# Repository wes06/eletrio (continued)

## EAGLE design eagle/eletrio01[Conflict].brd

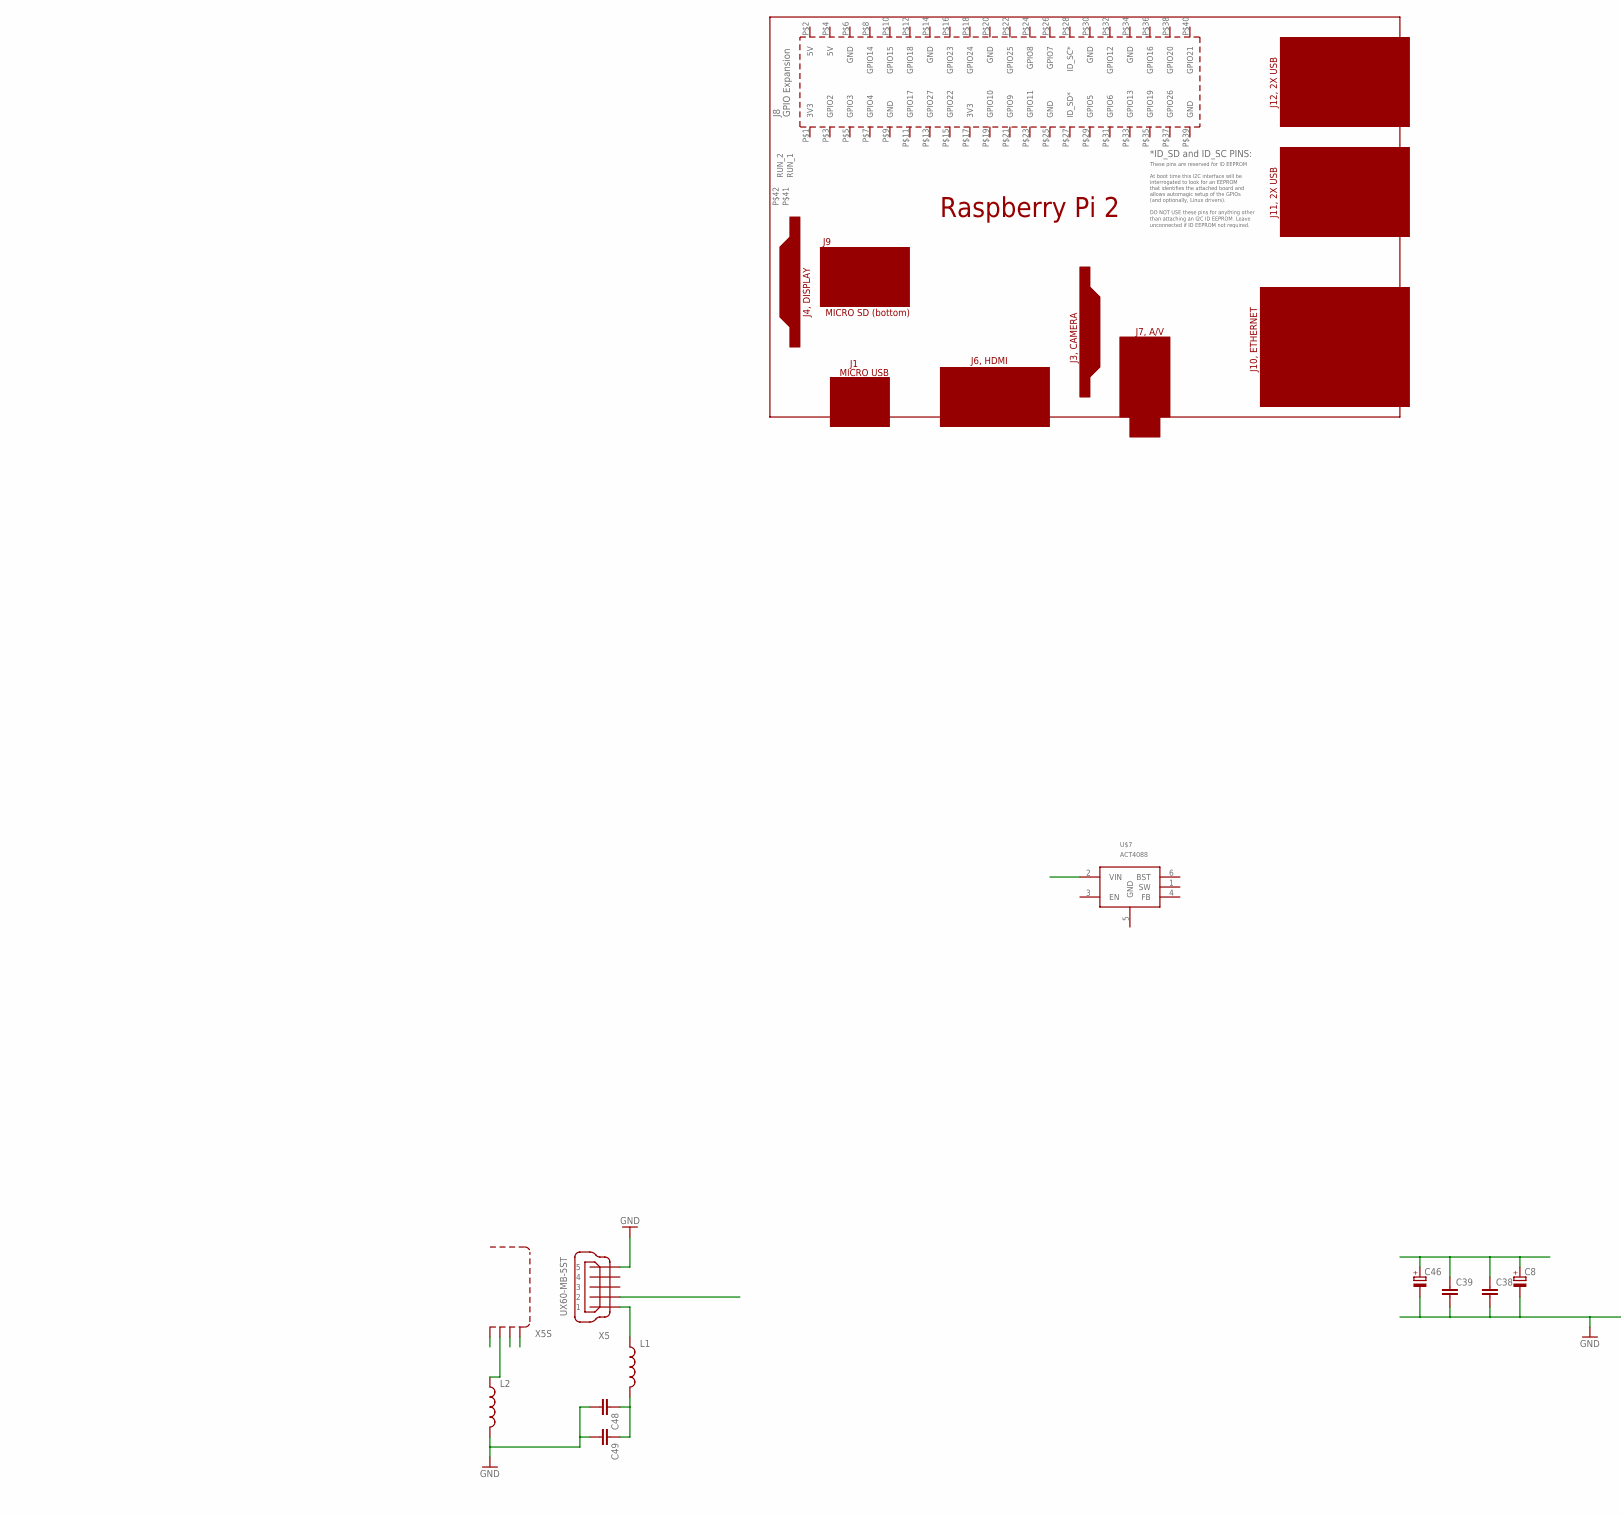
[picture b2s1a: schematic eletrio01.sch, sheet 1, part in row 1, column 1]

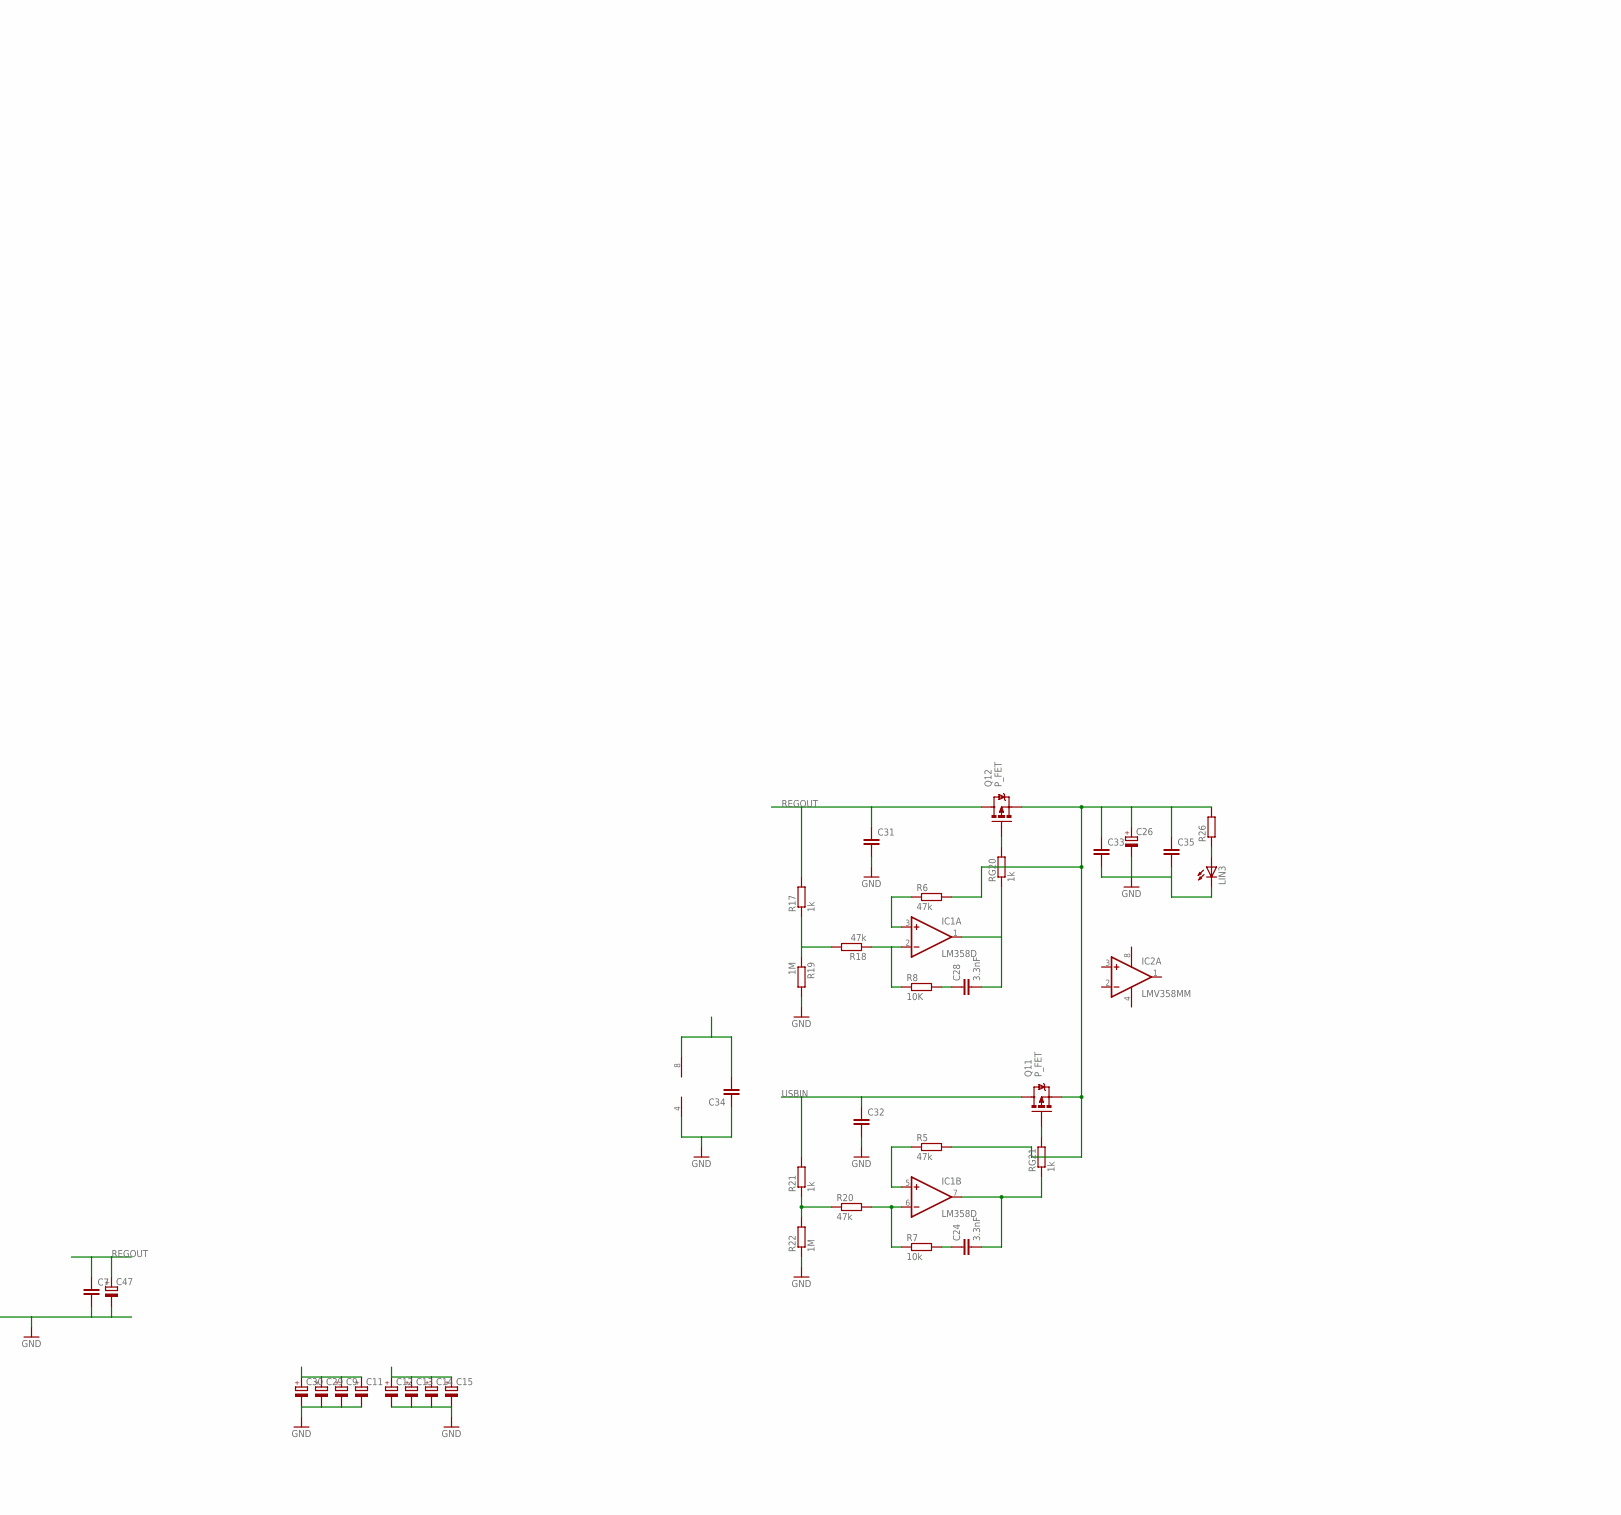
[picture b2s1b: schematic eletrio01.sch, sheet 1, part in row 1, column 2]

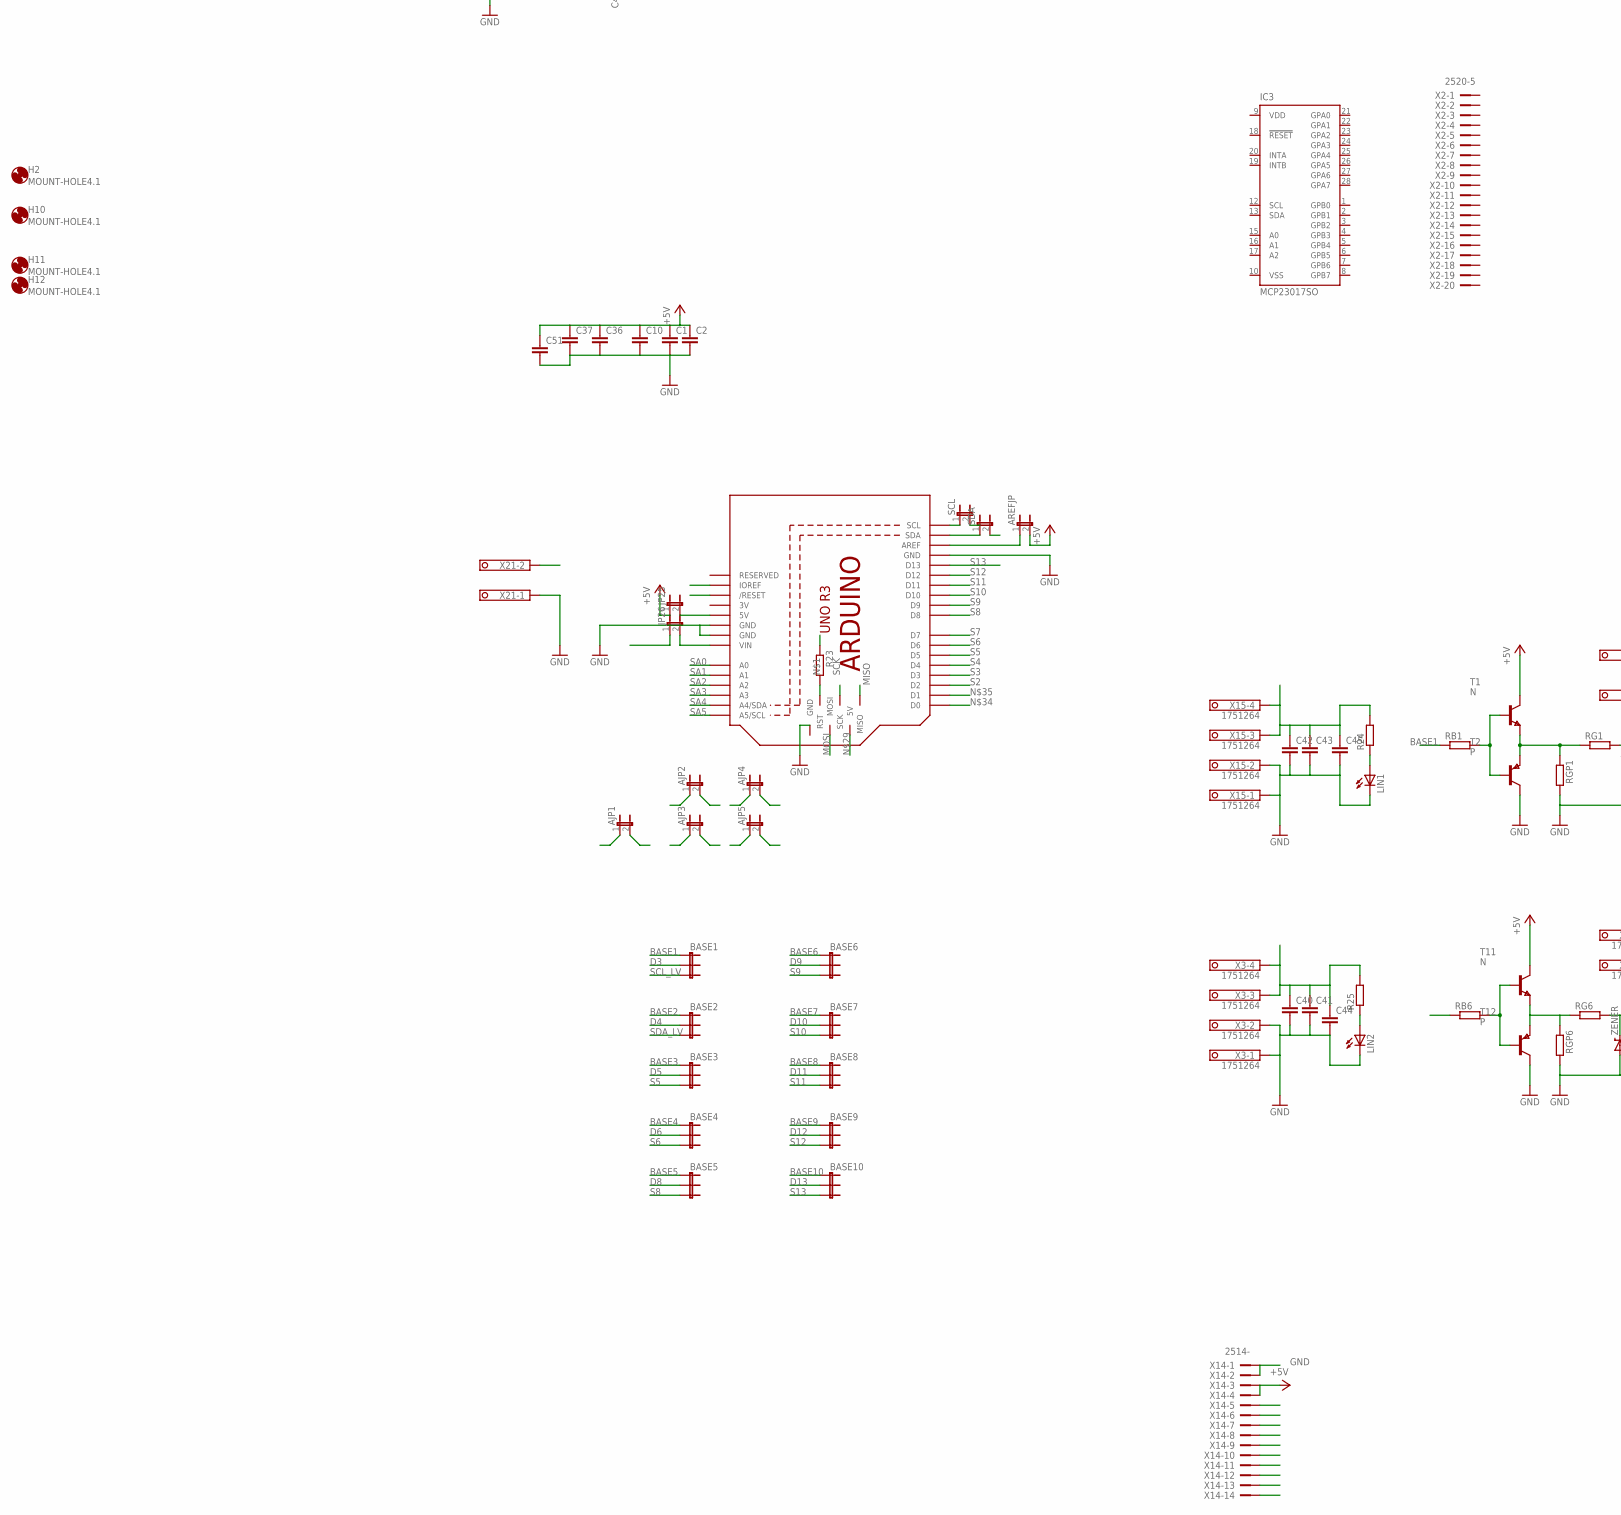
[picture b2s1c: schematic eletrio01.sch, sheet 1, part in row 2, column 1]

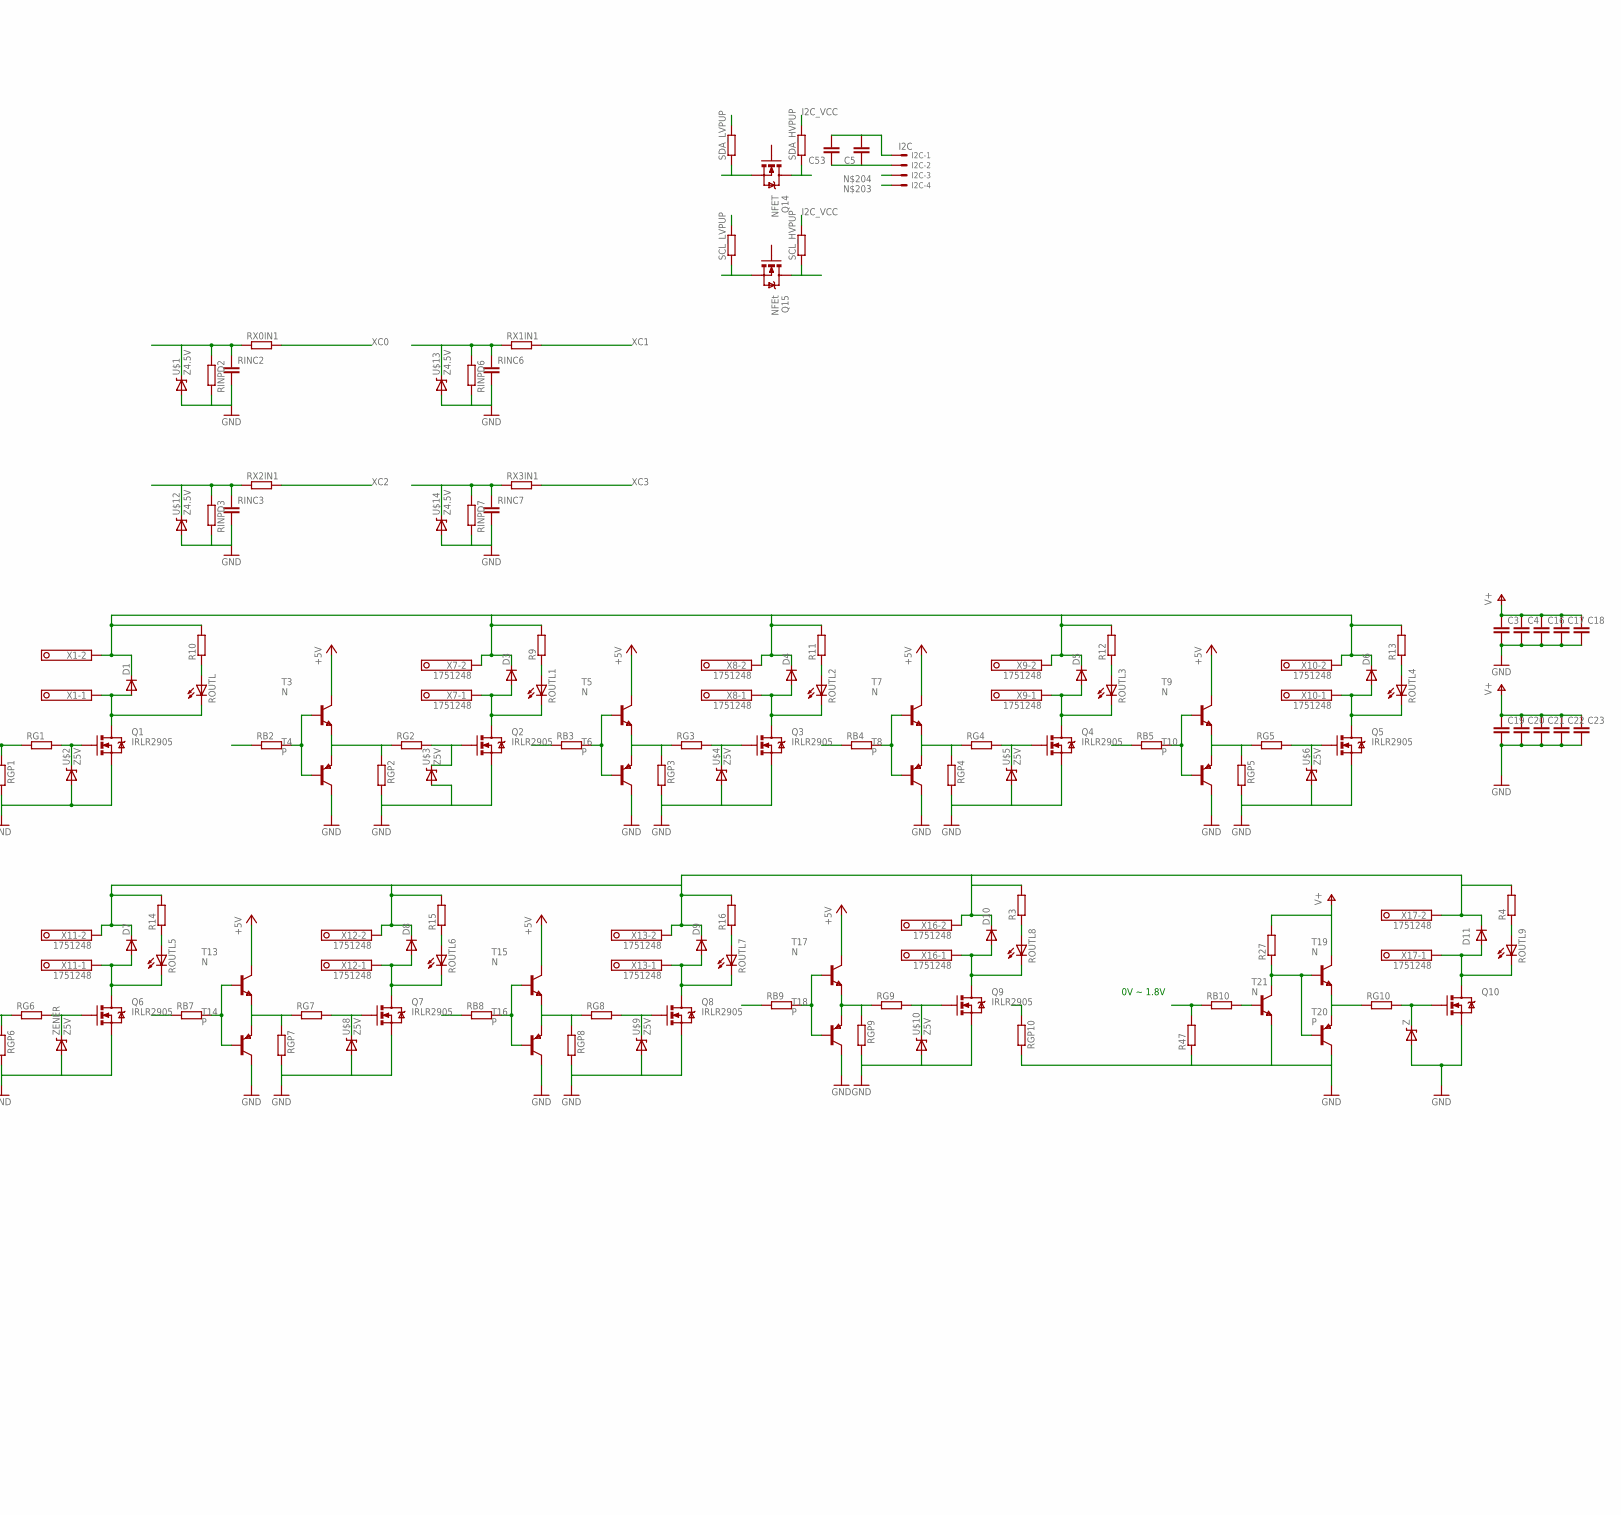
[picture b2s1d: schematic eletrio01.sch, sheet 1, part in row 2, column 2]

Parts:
AJP1, AJP2, AJP3, AJP4, AJP5: JUMPER-2SMD-NC; SJ_2S
AREFJP: JUMPER-2SMD-NC; SJ_2S
BASE1, BASE2, BASE3, BASE4, BASE5, BASE6, BASE7, BASE8, BASE9, BASE10: JUMPER-3PTH; 1X03
C1, C2, C5, C7, C10, C31, C32, C33, C34, C37, C38, C39, C40, C41, C42, C43, C48, C53: C-EUC0805; C0805
C3, C4, C16, C17, C18, C19, C20, C21, C22, C23: C-EUC0603; C0603
C8, C26, C46, C47: CPOL-EUUD-6,3X8,8; UD-6,3X5,8_NICHICON
C9, C11, C12, C13, C14, C15, C29, C30: CPOL-EUF; PANASONIC_F
C24, C28: 3.3nF; C0603
C35, C36, C49, C51: C-EUC1210; C1210
C44, C45: C-EU075-032X103; C075-032X103
D1, D3, D4, D5, D6, D7, D8, D9, D10, D11: DIODESMA-ALT; SMA-DIODE_ALT
H2, H10, H11, H12: MOUNT-HOLE4.1; 4,1
I2C: I2C; 22-23-2041
IC1: LM358D; SO08
IC2: LMV358MM; MSOP08
IC3: MCP23017SO; SO28W
JP25, JP26: JUMPER-2SMD-NC; SJ_2S
L1, L2: INDUCTOR0805; 0805
LIN1, LIN2, LIN3: LEDCHIP-LED0805; CHIP-LED0805
M1: ARDUINO_R3_ICSP; ARDUINOR3_ICSP
PCB1: RPI2
Q1, Q2, Q3, Q4, Q5, Q6, Q7, Q8, Q9: IRLR2905; DPAK
Q10: MOSFET-NCHANNELSI7820DN; POWERPAK1212-8
Q11, Q12: P_FET; SOT23-3
Q14: NFET; SOT23
Q15: NFEt; SOT23
R3, R4, R9, R10, R11, R12, R13, R14, R15, R16, R23, R24, R25, R26, R27, R47: R-EU_R0603; R0603
R5, R6, R18, R20: 47k; R0603
R7: 10k; R0603
R8: 10K; R0603
R17, R21: 1k; R0603
R19, R22: 1M; R0603
RB1, RB2, RB3, RB4, RB5, RB6, RB7, RB8, RB9, RB10: R-EU_R0603; R0603
RG1, RG2, RG3, RG4, RG5, RG6, RG7, RG8, RG9, RG10: R-EU_R0603; R0603
RG20, RG21: 1k; R0603
RGP1, RGP2, RGP3, RGP4, RGP5, RGP6, RGP7, RGP8, RGP9, RGP10: R-EU_R0603; R0603
RINC2, RINC3, RINC6, RINC7: C-EUC0805; C0805
RINPD2, RINPD3, RINPD6, RINPD7: R-EU_R0603; R0603
ROUTL, ROUTL1, ROUTL2, ROUTL3, ROUTL4, ROUTL5, ROUTL6, ROUTL7, ROUTL8, ROUTL9: LEDCHIP-LED0805; CHIP-LED0805
RX0IN1, RX1IN1, RX2IN1, RX3IN1: R-EU_R0805; R0805
SCL: JUMPER-2SMD-NC; SJ_2S
SCL_HVPUP: R-EU_R0805; R0805
SCL_LVPUP: R-EU_R0805; R0805
SDA: JUMPER-2SMD-NC; SJ_2S
SDA_HVPUP: R-EU_R0805; R0805
SDA_LVPUP: R-EU_R0805; R0805
T1, T3, T5, T7, T9, T11, T13, T15, T17, T19, T21: N; SOT323
T2, T4, T6, T8, T10, T12, T14, T16, T18, T20: P; SOT323
U$1, U$12, U$13, U$14: Z4.5V; SOD-323
U$2, U$3, U$4, U$5, U$6, U$8, U$9, U$10: Z5V; SOD-323
U$7: ACT4088; SOT23-6
X1, X7, X8, X9, X10, X11, X12, X13, X16, X17, X21: 1751248
X2: 2520-5; PAK100/2500-5-20
X3, X15: 1751264
X5: UX60-MB-5ST
X14: 2514-; PAK100/2500-14
Z: DIODE-ZENER-BZT52; SOD-323
ZENER: Z5V; SOD-323

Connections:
3V: M1.3V
+5V: AREFJP.2, C1.1, C2.1, C10.1, C26.+, C33.1, C34.2, C35.1, C36.1, C37.1, C51.1, IC1.8 (V+), JP25.1, Q11.2 (S), Q12.2 (S), R5.2, R6.2, R26.2, T1.1 (C), T3.1 (C), T5.1 (C), T7.1 (C), T9.1 (C), T11.1 (C), T13.1 (C), T15.1 (C), T17.1 (C), X14.3, X14.4
A1: AJP1.2
A2: AJP2.2
A3: AJP3.2
A4: AJP4.2, SDA.2
A5: AJP5.2, SCL.2
ARDVIN: C8.+, C38.1, C39.1, C46.+, JP26.1, X21.2
BASE1: BASE1.1, RB1.1, X14.5
BASE2: BASE2.1, RB2.1, X14.6
BASE3: BASE3.1, RB3.1, X14.7
BASE4: BASE4.1, RB4.1, X14.8
BASE5: BASE5.1, RB5.1, X14.9
BASE6: BASE6.1, RB6.1, X14.10
BASE7: BASE7.1, RB7.1, X14.11
BASE8: BASE8.1, RB8.1, X14.12
BASE9: BASE9.1, RB9.1, X14.13
BASE10: BASE10.1, RGP10.1, X14.14
D3: BASE1.2
D4: BASE2.2
D5: BASE3.2
D6: BASE4.2
D8: BASE5.2
D9: BASE6.2
D10: BASE7.2
D11: BASE8.2
D12: BASE9.2
D13: BASE10.2
GND: C3.2, C4.2, C5.2, C7.2, C8.-, C9.-, C11.-, C12.-, C13.-, C14.-, C15.-, C16.2, C17.2, C18.2, C19.2, C20.2, C21.2, C22.2, C23.2, C26.-, C29.-, C30.-, C31.2, C32.2, C33.2, C34.1, C35.2, C38.2, C39.2, C40.2, C41.2, C42.2, C43.2, C44.2, C45.2, C46.-, C47.-, C48.2, C49.2, C53.2, I2C.1, IC1.4 (V-), L2.2, LIN1.C, LIN2.C, LIN3.C, M1.GND, M1.GND@1 (GND), M1.GND@3 (GND), Q1.3 (S), Q2.3 (S), Q3.3 (S), Q4.3 (S), Q5.3 (S), Q6.3 (S), Q7.3 (S), Q8.3 (S), Q9.3 (S), Q10.S1 (S), Q10.S2 (S), Q10.S3 (S), R19.2, R22.1, R47.1, RGP1.2, RGP2.2, RGP3.2, RGP4.2, RGP5.2, RGP6.2, RGP7.2, RGP8.2, RGP9.2, RGP10.2, RINC2.2, RINC3.2, RINC6.2, RINC7.2, RINPD2.2, RINPD3.2, RINPD6.2, RINPD7.2, T2.1 (C), T4.1 (C), T6.1 (C), T8.1 (C), T10.1 (C), T12.1 (C), T14.1 (C), T16.1 (C), T18.1 (C), T20.1 (C), T21.3 (E), U$1.2 (A), U$2.2 (A), U$3.2 (A), U$4.2 (A), U$5.2 (A), U$6.2 (A), U$8.2 (A), U$9.2 (A), U$10.2 (A), U$12.2 (A), U$13.2 (A), U$14.2 (A), X3.1, X3.2, X5.5, X14.1, X14.2, X15.1, X15.2, X21.1, Z.2 (A), ZENER.2 (A); also elsewhere on the board
I2C_VCC: C5.1, C53.1, I2C.2, SCL_HVPUP.2, SDA_HVPUP.2
MISO: M1.MISO
MOSI: M1.MOSI
unnamed: M1.RESET_ICSP (RST), R23.2
unnamed: C1.2, C2.2, C10.2, C36.2, C37.2, C51.2
unnamed: RB10.2, T21.2 (B)
unnamed: L2.1, X5.M2 (S2)
unnamed: IC1.5 (+IN), R5.1
unnamed: LIN1.A, R24.1
unnamed: M1.SCL, SCL.1
unnamed: AREFJP.1, M1.AREF
unnamed: JP25.2, M1.5V
unnamed: R47.2, RB10.1
unnamed: C24.2, IC1.7 (OUT), RG21.1
unnamed: IC1.3 (+IN), R6.1
unnamed: M1.SDA, SDA.1
unnamed: IC1.6 (-IN), R7.1, R20.2
unnamed: IC1.2 (-IN), R8.1, R18.1
unnamed: C28.1, R8.2
unnamed: C24.1, R7.2
unnamed: R17.1, R18.2, R19.1
unnamed: LIN2.A, R25.1
unnamed: LIN3.A, R26.1
unnamed: L1.1, X5.1
unnamed: R20.1, R21.1, R22.2
unnamed: JP26.2, M1.VIN
unnamed: D3.A, Q2.4 (D), ROUTL1.C, X7.1
unnamed: Q2.1 (G), RG2.2, U$3.1 (C)
unnamed: R9.1, ROUTL1.A
unnamed: D4.A, Q3.4 (D), ROUTL2.C, X8.1
unnamed: Q3.1 (G), RG3.2, U$4.1 (C)
unnamed: R11.1, ROUTL2.A
unnamed: Q11.1 (G), RG21.2
unnamed: Q1.1 (G), RG1.2, U$2.1 (C)
unnamed: Q4.1 (G), RG4.2, U$5.1 (C)
unnamed: Q12.1 (G), RG20.2
unnamed: R12.1, ROUTL3.A
unnamed: D6.A, Q5.4 (D), ROUTL4.C, X10.1
unnamed: Q5.1 (G), RG5.2, U$6.1 (C)
unnamed: R13.1, ROUTL4.A
unnamed: C28.2, IC1.1 (OUT), RG20.1
unnamed: D1.A, Q1.4 (D), ROUTL.C, X1.1
unnamed: R10.1, ROUTL.A
unnamed: RB1.2, T1.2 (B), T2.2 (B)
unnamed: RB2.2, T3.2 (B), T4.2 (B)
unnamed: D10.A, Q9.4 (D), ROUTL8.C, X16.1
unnamed: Q9.1 (G), RG9.2, U$10.1 (C)
unnamed: R3.1, ROUTL8.A
unnamed: D11.A, Q10.D1 (D), Q10.D2 (D), Q10.D3 (D), Q10.D4 (D), Q10.DPAD (D), ROUTL9.C, X17.1
unnamed: Q10.G, RG10.2, Z.1 (C)
unnamed: R4.1, ROUTL9.A
unnamed: RG1.1, RGP1.1, T1.3 (E), T2.3 (E)
unnamed: RB3.2, T5.2 (B), T6.2 (B)
unnamed: RB4.2, T7.2 (B), T8.2 (B)
unnamed: RB5.2, T9.2 (B), T10.2 (B)
unnamed: RB6.2, T11.2 (B), T12.2 (B)
unnamed: RB7.2, T13.2 (B), T14.2 (B)
unnamed: RB8.2, T15.2 (B), T16.2 (B)
unnamed: D7.A, Q6.4 (D), ROUTL5.C, X11.1
unnamed: RB9.2, T17.2 (B), T18.2 (B)
unnamed: R27.1, T19.2 (B), T20.2 (B), T21.1 (C)
unnamed: Q6.1 (G), RG6.2, ZENER.1 (C)
unnamed: R14.1, ROUTL5.A
unnamed: D8.A, Q7.4 (D), ROUTL6.C, X12.1
unnamed: Q7.1 (G), RG7.2, U$8.1 (C)
unnamed: R15.1, ROUTL6.A
unnamed: D9.A, Q8.4 (D), ROUTL7.C, X13.1
unnamed: Q8.1 (G), RG8.2, U$9.1 (C)
unnamed: R16.1, ROUTL7.A
POWERBUS_A: C9.+, C11.+, C29.+, C30.+, C40.1, C41.1, C44.1, D7.C, D8.C, D9.C, D10.C, D11.C, R3.2, R4.2, R14.2, R15.2, R16.2, R25.2, X3.3, X3.4, X11.2, X12.2, X13.2, X16.2, X17.2
POWERBUS_B: C12.+, C13.+, C14.+, C15.+, C42.1, C43.1, C45.1, D1.C, D3.C, D4.C, D5.C, D6.C, R9.2, R10.2, R11.2, R12.2, R13.2, R24.2, X1.2, X7.2, X8.2, X9.2, X10.2, X15.3, X15.4
Q4: D5.A, Q4.4 (D), ROUTL3.C, X9.1
REGOUT: C7.1, C31.1, C47.+, Q12.3 (D), R17.2
RG1: RG9.1, RGP9.1, T17.3 (E), T18.3 (E)
RG2: RG2.1, RGP2.1, T3.3 (E), T4.3 (E)
RG3: RG3.1, RGP3.1, T5.3 (E), T6.3 (E)
RG4: RG4.1, RGP4.1, T7.3 (E), T8.3 (E)
RG5: RG5.1, RGP5.1, T9.3 (E), T10.3 (E)
RG6: RG6.1, RGP6.1, T11.3 (E), T12.3 (E)
RG7: RG7.1, RGP7.1, T13.3 (E), T14.3 (E)
RG8: RG8.1, RGP8.1, T15.3 (E), T16.3 (E)
RG9: RG10.1, T19.3 (E), T20.3 (E)
RST: R23.1
S2: M1.D2
S3: M1.D3
S4: M1.D4
S5: BASE3.3, M1.D5
S6: BASE4.3, M1.D6
S7: M1.D7
S8: BASE5.3, M1.D8
S9: BASE6.3, M1.D9
S10: BASE7.3, M1.D10
S11: BASE8.3, M1.D11
S12: BASE9.3, M1.D12
S13: BASE10.3, M1.D13
SA0: M1.A0
SA1: AJP1.1, M1.A1
SA2: AJP2.1, M1.A2
SA3: AJP3.1, M1.A3
SA4: AJP4.1, M1.A4 (A4/SDA)
SA5: AJP5.1, M1.A5 (A5/SCL)
SCK: M1.SCK
SCL_LV: BASE1.3, Q15.2 (S), SCL_LVPUP.1
SDA_HV: Q14.3 (D), Q15.3 (D), SCL_HVPUP.1, SDA_HVPUP.1
SDA_LV: BASE2.3, Q14.2 (S), SDA_LVPUP.1
SHIELD1: X5.M4 (S4)
SHIELD2: X5.M3 (S3)
SHIELD3: X5.M1 (S1)
USBIN: C32.1, C48.1, C49.1, L1.2, Q11.3 (D), R21.2
V+: C3.1, C4.1, C16.1, C17.1, C18.1, C19.1, C20.1, C21.1, C22.1, C23.1, IC2.8 (V+), R27.2, T19.1 (C)
V-: IC2.4 (V-)
VDD: IC3.9 (VDD); also elsewhere on the board
VSS: IC3.10 (VSS)
X0: RINC2.1, RINPD2.1, RX0IN1.1, U$1.1 (C)
X1: RINC6.1, RINPD6.1, RX1IN1.1, U$13.1 (C)
X2: RINC3.1, RINPD3.1, RX2IN1.1, U$12.1 (C)
X3: RINC7.1, RINPD7.1, RX3IN1.1, U$14.1 (C)
XC0: RX0IN1.2
XC1: RX1IN1.2
XC2: RX2IN1.2
XC3: RX3IN1.2

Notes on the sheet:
0V ~ 1.8V

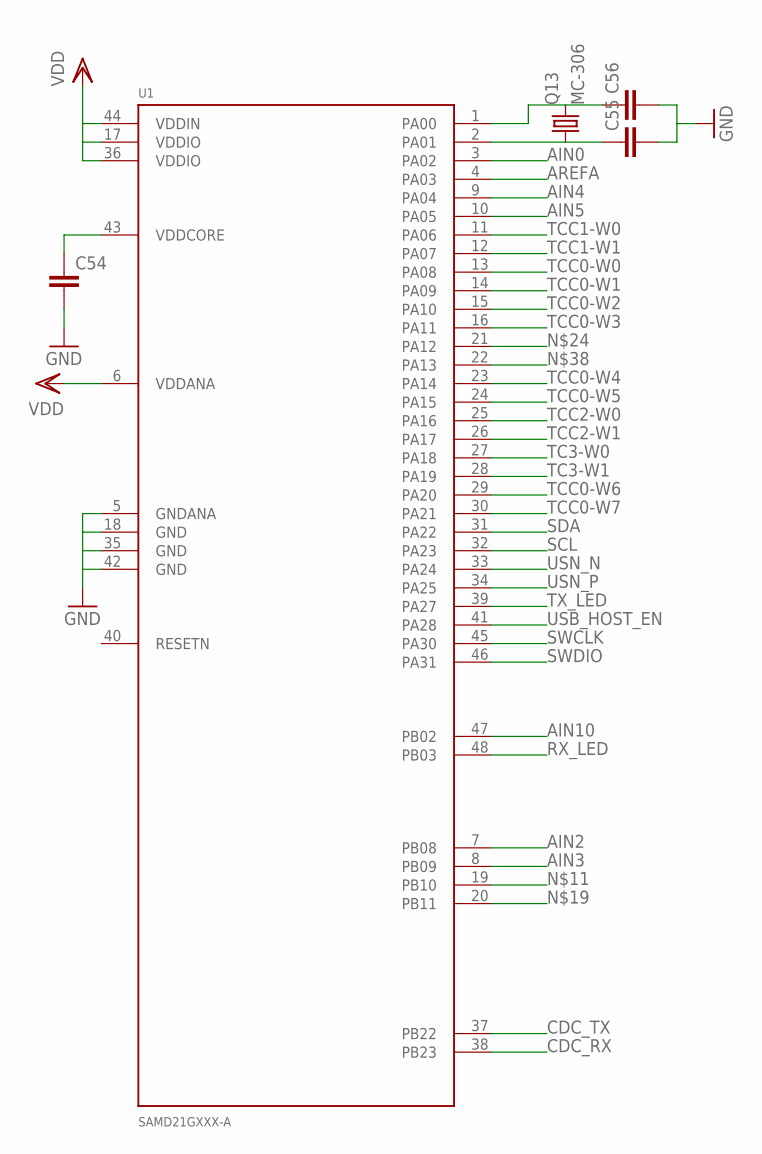
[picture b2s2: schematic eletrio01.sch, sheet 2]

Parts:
C54, C55, C56: C-EUC0603; C0603
Q13: MC-306
U1: SAMD21GXXX-A; TQFP48

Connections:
AIN0: U1.3 (PA02)
AIN2: U1.7 (PB08)
AIN3: U1.8 (PB09)
AIN4: U1.9 (PA04)
AIN5: U1.10 (PA05)
AIN10: U1.47 (PB02)
AREFA: U1.4 (PA03)
CDC_RX: U1.38 (PB23)
CDC_TX: U1.37 (PB22)
GND: C54.2, C55.2, C56.2, U1.5 (GNDANA), U1.18 (GND), U1.35 (GND), U1.42 (GND); also elsewhere on the board
unnamed: C55.1, Q13.1, U1.2 (PA01)
unnamed: C56.1, Q13.4 (2), U1.1 (PA00)
RX_LED: U1.48 (PB03)
SCL: U1.32 (PA23)
SDA: U1.31 (PA22)
SWCLK: U1.45 (PA30)
SWDIO: U1.46 (PA31)
TC3-W0: U1.27 (PA18)
TC3-W1: U1.28 (PA19)
TCC0-W0: U1.13 (PA08)
TCC0-W1: U1.14 (PA09)
TCC0-W2: U1.15 (PA10)
TCC0-W3: U1.16 (PA11)
TCC0-W4: U1.23 (PA14)
TCC0-W5: U1.24 (PA15)
TCC0-W6: U1.29 (PA20)
TCC0-W7: U1.30 (PA21)
TCC1-W0: U1.11 (PA06)
TCC1-W1: U1.12 (PA07)
TCC2-W0: U1.25 (PA16)
TCC2-W1: U1.26 (PA17)
TX_LED: U1.39 (PA27)
USB_HOST_EN: U1.41 (PA28)
USN_N: U1.33 (PA24)
USN_P: U1.34 (PA25)
VDD: U1.6 (VDDANA), U1.17 (VDDIO), U1.36 (VDDIO), U1.44 (VDDIN); also elsewhere on the board
VDDCORE: C54.1, U1.43 (VDDCORE)

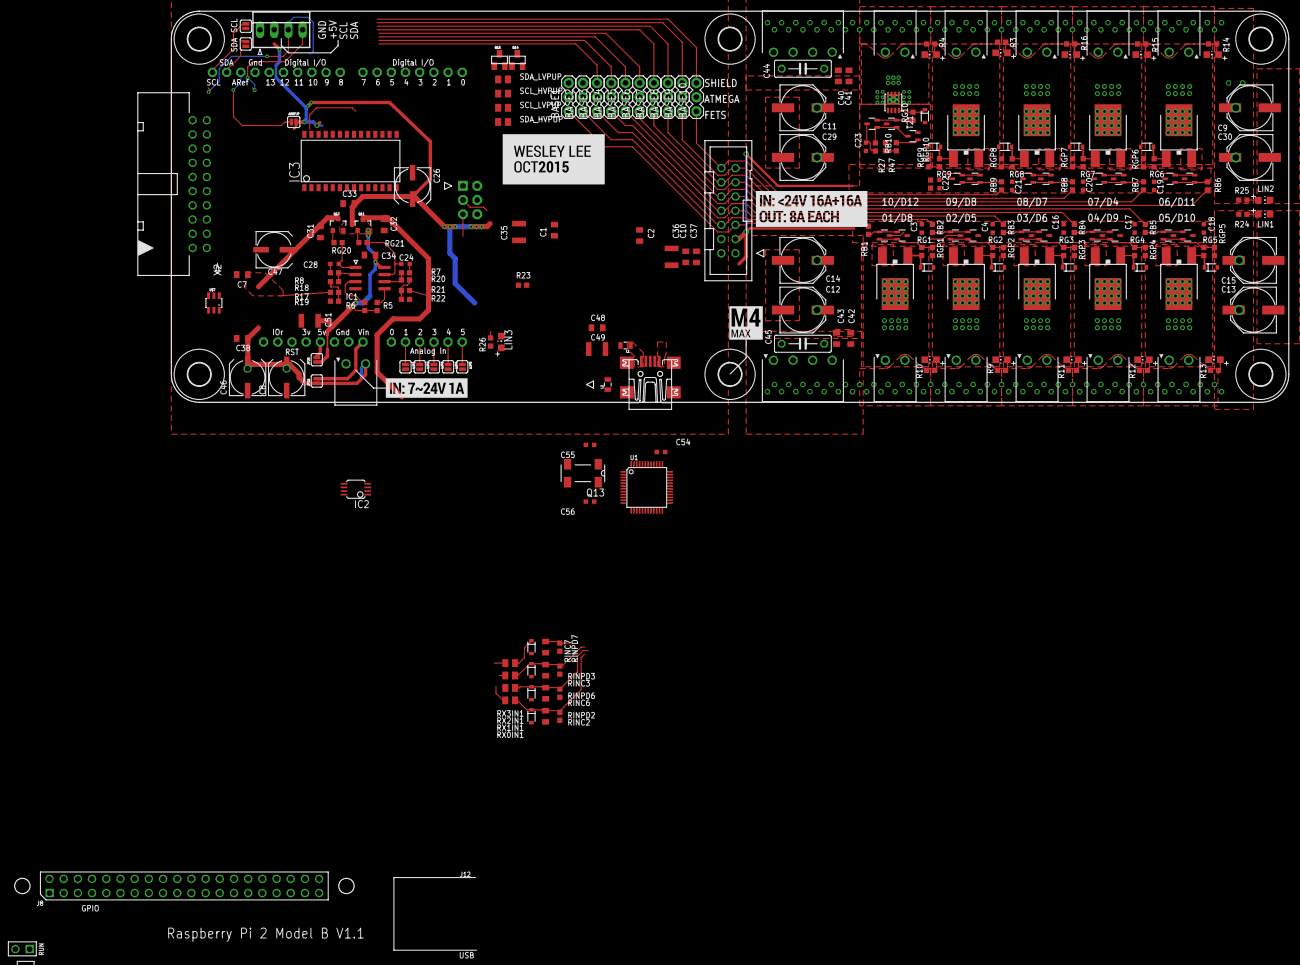
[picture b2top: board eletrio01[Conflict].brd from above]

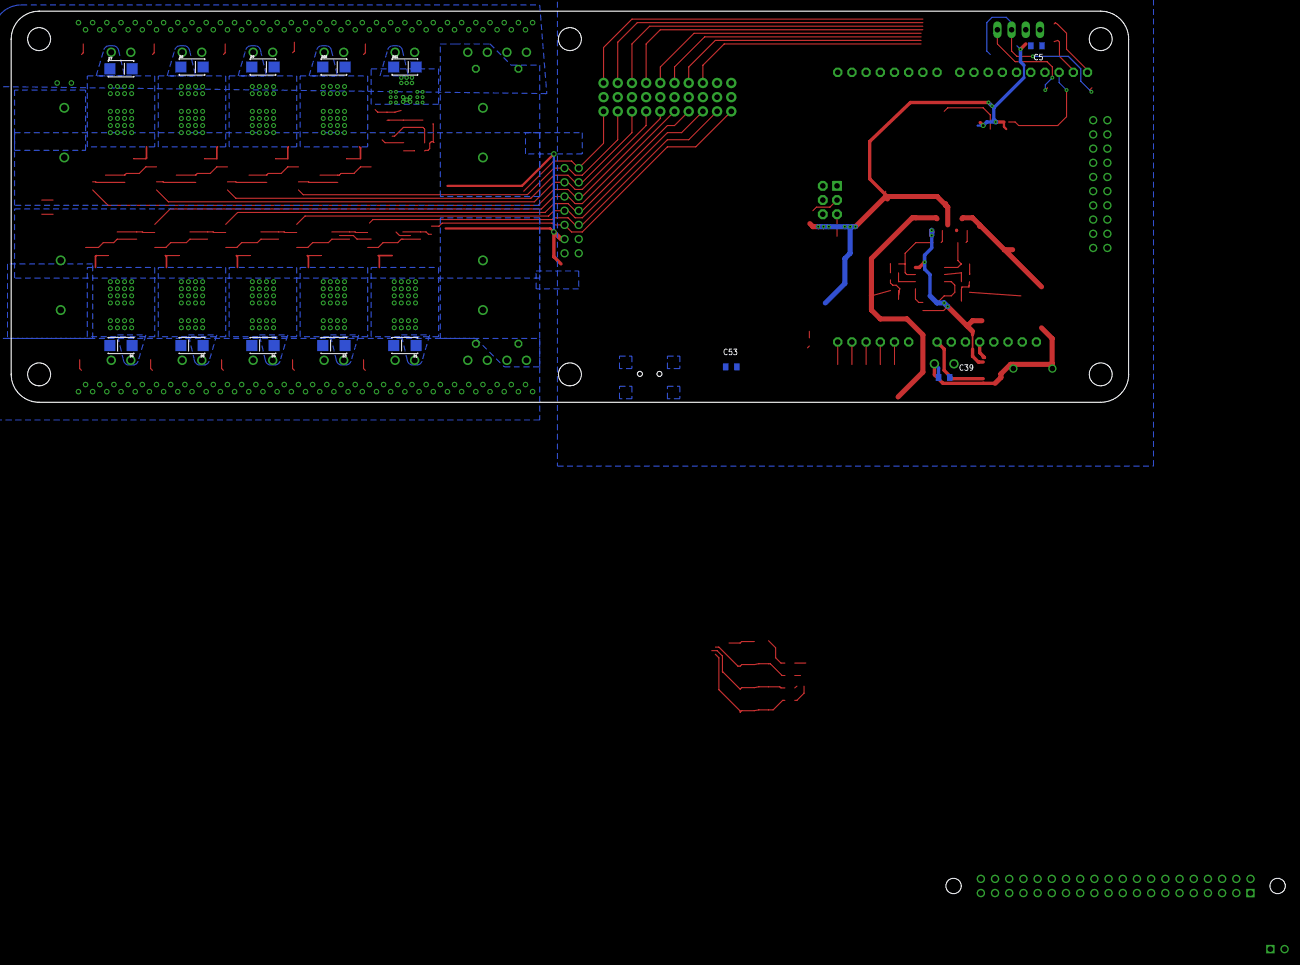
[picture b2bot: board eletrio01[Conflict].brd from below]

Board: 2 copper layers, 200.0 x 70.0 mm, 250 parts (13 on the bottom side), 121 nets.

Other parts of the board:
H1, H9: MOUNT-HOLE4.1; 4,1
